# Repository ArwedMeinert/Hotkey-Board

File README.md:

# Hotkey-Board
All the needed Information for the Hotkey-Board
It includes the Schematics of the Hardware, the PCB- Layout and the Code for the actual microcontroller. 
Feel free to make your own changes and improve on what’s already there. 
All the uploaded Files (excluding the libraries in the Arduino IDE) were created by me.

After the design of the PCB, I got it made and soldert all parts on it. Luckily, everything worked at the first try.

Each button can be individually programmed. You can add more than one profile and add an individual colour to each profile (every button is individually backlit and be individually addressed). A button press gets visualized by the sudden change of colour, that then fades back to the standard colour of the profile within 200 ms (this also helps with the debounce time of the buttons).

This version of the Hotkey-Board doesn't support anti-ghosting (using diodes for the button matrix). This could be an improvement left for a second version as well as a little OLED display to display various functions of the keys. 
## Case
After a few months in use I descided to add a case for the pcb to make it easier to carry around (and because I got access to a 3D Printer).

All the files are available to download. The case now also includes holes for the hinges as well as magnets embedded in the lid to make it stay closed but still easy enough to open.

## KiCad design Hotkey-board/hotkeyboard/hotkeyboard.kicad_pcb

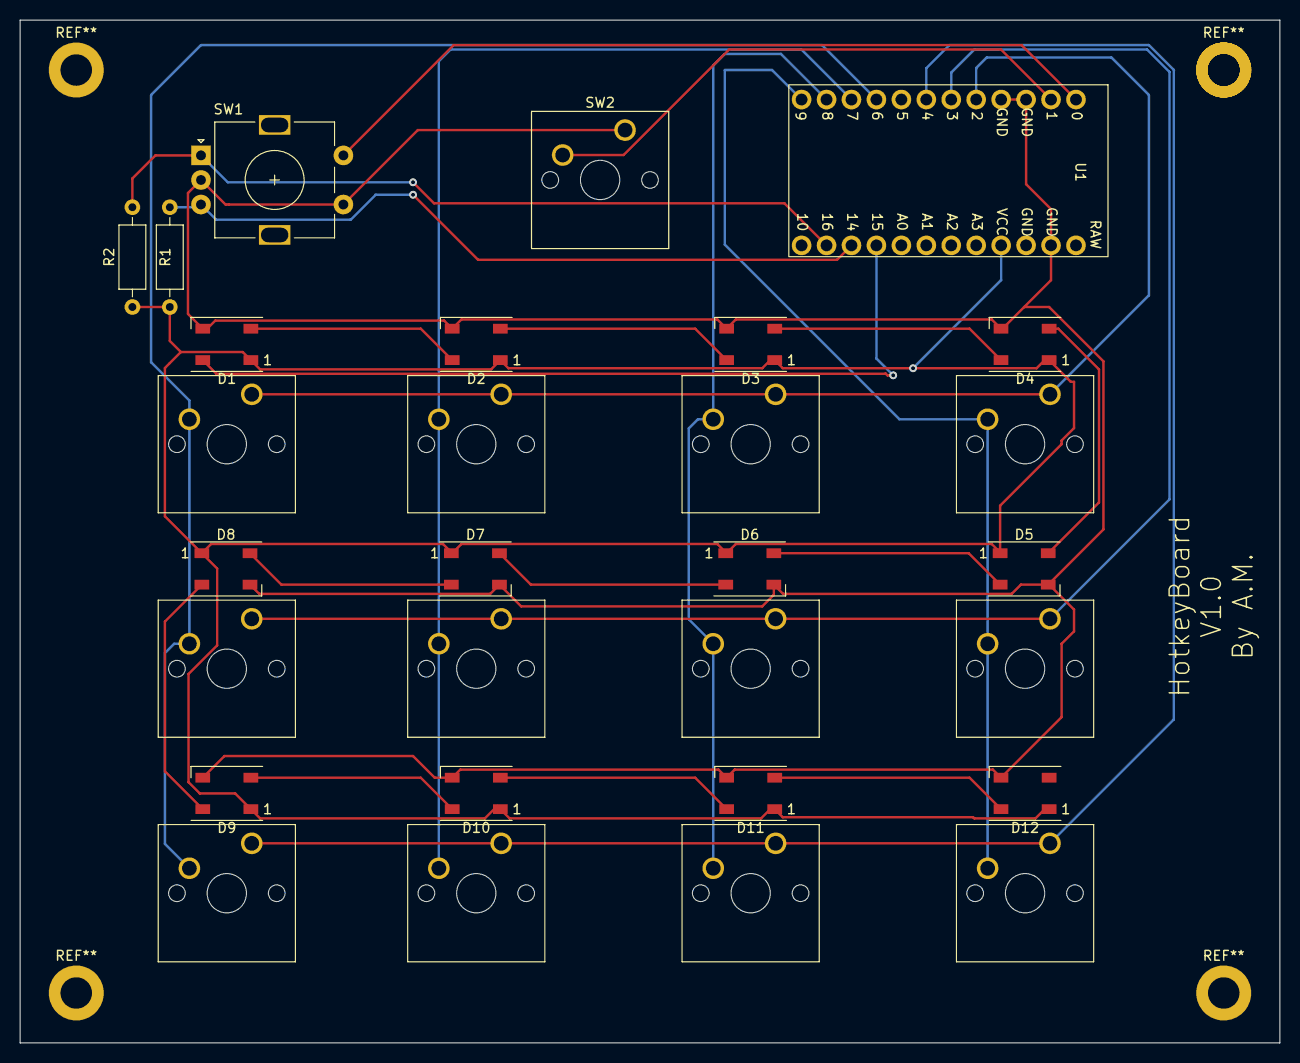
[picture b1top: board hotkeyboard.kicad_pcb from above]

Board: 2 copper layers, 128.3 x 104.1 mm, 17 parts (0 on the bottom side), 18 nets.

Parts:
D1, D2, D3, D4, D5, D6, D7, D8, D9, D10, D11, D12: WS2812B; LED_WS2812B_PLCC4_5.0x5.0mm_P3.2mm
R1, R2: R_Axial_DIN0207_L6.3mm_D2.5mm_P10.16mm_Horizontal
SW1: RotaryEncoder_Switch; RotaryEncoder_Alps_EC11E-Switch_Vertical_H20mm
SW2: SW_MEC_5G; SW_Cherry_MX_1.00u_PCB
U1: ARCELI_Pro_Micro; ARCELI ATmega32U4

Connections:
+5V: D1.1 (VDD), D2.1 (VDD), D3.1 (VDD), D4.1 (VDD), D5.1 (VDD), D6.1 (VDD), D7.1 (VDD), D8.1 (VDD), D9.1 (VDD), D10.1 (VDD), D11.1 (VDD), D12.1 (VDD), R1.1, R2.1, U1.VCC
GND: D1.3 (VSS), D2.3 (VSS), D3.3 (VSS), D4.3 (VSS), D5.3 (VSS), D6.3 (VSS), D7.3 (VSS), D8.3 (VSS), D9.3 (VSS), D10.3 (VSS), D11.3 (VSS), D12.3 (VSS), SW1.C, SW1.S1, SW2.1, U1.GND
unnamed: D1.2 (DOUT), D2.4 (DIN)
unnamed: D2.2 (DOUT), D3.4 (DIN)
unnamed: D3.2 (DOUT), D4.4 (DIN)
unnamed: D4.2 (DOUT), D5.4 (DIN)
unnamed: D5.2 (DOUT), D6.4 (DIN)
unnamed: D6.2 (DOUT), D7.4 (DIN)
unnamed: D7.2 (DOUT), D8.4 (DIN)
unnamed: D8.2 (DOUT), D9.4 (DIN)
unnamed: D10.2 (DOUT), D11.4 (DIN)
unnamed: D9.2 (DOUT), D10.4 (DIN)
unnamed: D11.2 (DOUT), D12.4 (DIN)
buttonencoder: SW1.S2, U1.0 (TX0)
caseswitch: SW2.2, U1.1 (RX1)
clk: R2.2, SW1.A, U1.16
dt: R1.2, SW1.B, U1.14
neopixel: D1.4 (DIN), U1.15
